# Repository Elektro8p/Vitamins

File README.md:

# Vitamins

This is the folder that I keep everything for all my projects in…

There are details about this folder and such on my blog @ <http://skippy.org.uk/guides/arduino/my-library-folder>

At some point I will work out how to do sub modules or something to referance things which are stored in git elsewhere

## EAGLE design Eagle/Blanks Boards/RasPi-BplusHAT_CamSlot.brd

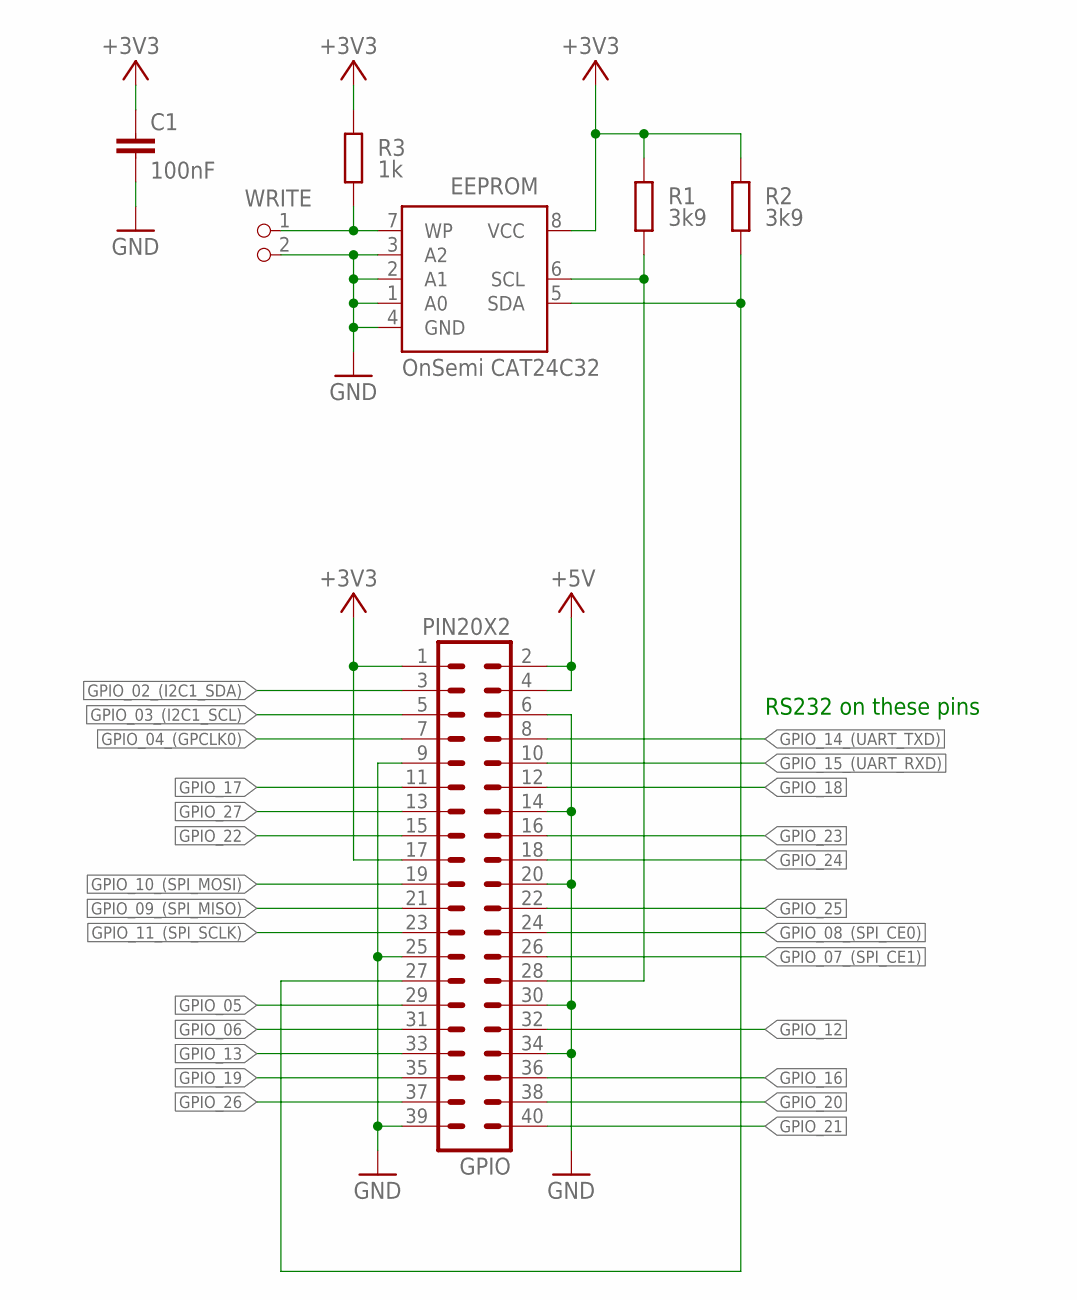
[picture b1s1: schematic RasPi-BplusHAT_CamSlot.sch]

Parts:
C1: 100nF; C0805K
EEPROM: OnSemi CAT24C32; SOIC8
GPIO: PIN20X2; PIN_20X2
R1, R2: 3k9; M0805; TOLERANCE 5%
R3: 1k; M0805; TOLERANCE 5%
WRITE: PIN2_100; PIN_W_2

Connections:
+3V3: C1.1, EEPROM.8 (VCC), GPIO.1, GPIO.17, R1.2, R2.2, R3.2
+5V: GPIO.2, GPIO.4
GND: C1.2, EEPROM.1 (A0), EEPROM.2 (A1), EEPROM.3 (A2), EEPROM.4 (GND), GPIO.6, GPIO.9, GPIO.14, GPIO.20, GPIO.25, GPIO.30, GPIO.34, GPIO.39, WRITE.2
GPIO_02_(I2C1_SDA): GPIO.3
GPIO_03_(I2C1_SCL): GPIO.5
GPIO_04_(GPCLK0): GPIO.7
GPIO_05: GPIO.29
GPIO_06: GPIO.31
GPIO_07_(SPI_CE1): GPIO.26
GPIO_08_(SPI_CE0): GPIO.24
GPIO_09_(SPI_MISO): GPIO.21
GPIO_10_(SPI_MOSI): GPIO.19
GPIO_11_(SPI_SCLK): GPIO.23
GPIO_12: GPIO.32
GPIO_13: GPIO.33
GPIO_14_(UART_TXD): GPIO.8
GPIO_15_(UART_RXD): GPIO.10
GPIO_16: GPIO.36
GPIO_17: GPIO.11
GPIO_18: GPIO.12
GPIO_19: GPIO.35
GPIO_20: GPIO.38
GPIO_21: GPIO.40
GPIO_22: GPIO.15
GPIO_23: GPIO.16
GPIO_24: GPIO.18
GPIO_25: GPIO.22
GPIO_26: GPIO.37
GPIO_27: GPIO.13
ID_SC: EEPROM.6 (SCL), GPIO.28, R1.1
ID_SD: EEPROM.5 (SDA), GPIO.27, R2.1
WWPROM_WP: EEPROM.7 (WP), R3.1, WRITE.1

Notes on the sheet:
RS232 on these pins

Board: 2 copper layers, 7 parts (0 on the bottom side), 6 nets, no tracks yet.

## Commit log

2015-08-10 Created a Readme file
2015-08-12 Added MegaServo
2015-08-18 MP3 sheild added
2015-09-18 Clean up
2015-09-18 more clean up
2015-10-16 added some new Arduino Librarys
2015-10-16 added the command
2015-10-16 added another lib
